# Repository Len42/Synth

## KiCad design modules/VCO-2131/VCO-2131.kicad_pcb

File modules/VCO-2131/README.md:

# Analog VCO

## 10HP Eurorack Module

### Features
- Analog VCO with sawtooth, triangle, and square/pulse outputs
- Sub-oscillator square wave output
- Pitch, modulation, PWM, and sync CV inputs
- Coarse/fine tuning knobs and +/- 2-octave switch
- Based on an [SSI2131 VCO chip](https://soundsemiconductor.com/downloads/ssi2131datasheet.pdf)
- Volt-per-octave tracking over 10 octaves
- 1V/octave input can default to the Eurorack bus CV line (jumper-selectable) - more info [here](https://lenp.net/synth/eurorack-bus-cv-gate.html)

### Notes
This module requires a 16-pin Eurorack power cable, but it does not depend on +5V power from the Eurorack system.

[Here are instructions for calibration](https://lenp.net/synth/vco-calibration.html) of the VCO for proper 1V/octave tracking.

[TODO: old link for testing](calibration.md)

PCB layouts are provided in KiCad and gerber formats.
A drilling template is provided for the front panel.

The PCBs that I used can be ordered from OSH Park. The designs are here:
- [Controls board](https://oshpark.com/shared_projects/8MjA3NoD)
- [Middle board](https://oshpark.com/shared_projects/c16FyR7y) (Note: This is an older version of the PCB. The sub-oscillator circuit does not work on this version.)
- [Back board](https://oshpark.com/shared_projects/S84ptGBY)

Please note that I am a hobbyist, not a trained electronics engineer. No guarantees!

### Software Used

[KiCad](https://www.kicad.org/) 6.0.8

<hr /><div><div style="float:left; padding-right:10px;"></div><div style="xfloat:left; padding-left:10px;"><br />© 2022 Len Popp CC BY<br />This work is licensed under a <a rel="license" href="http://creativecommons.org/licenses/by/4.0/">Creative Commons Attribution 4.0 International License</a>.</div></div>

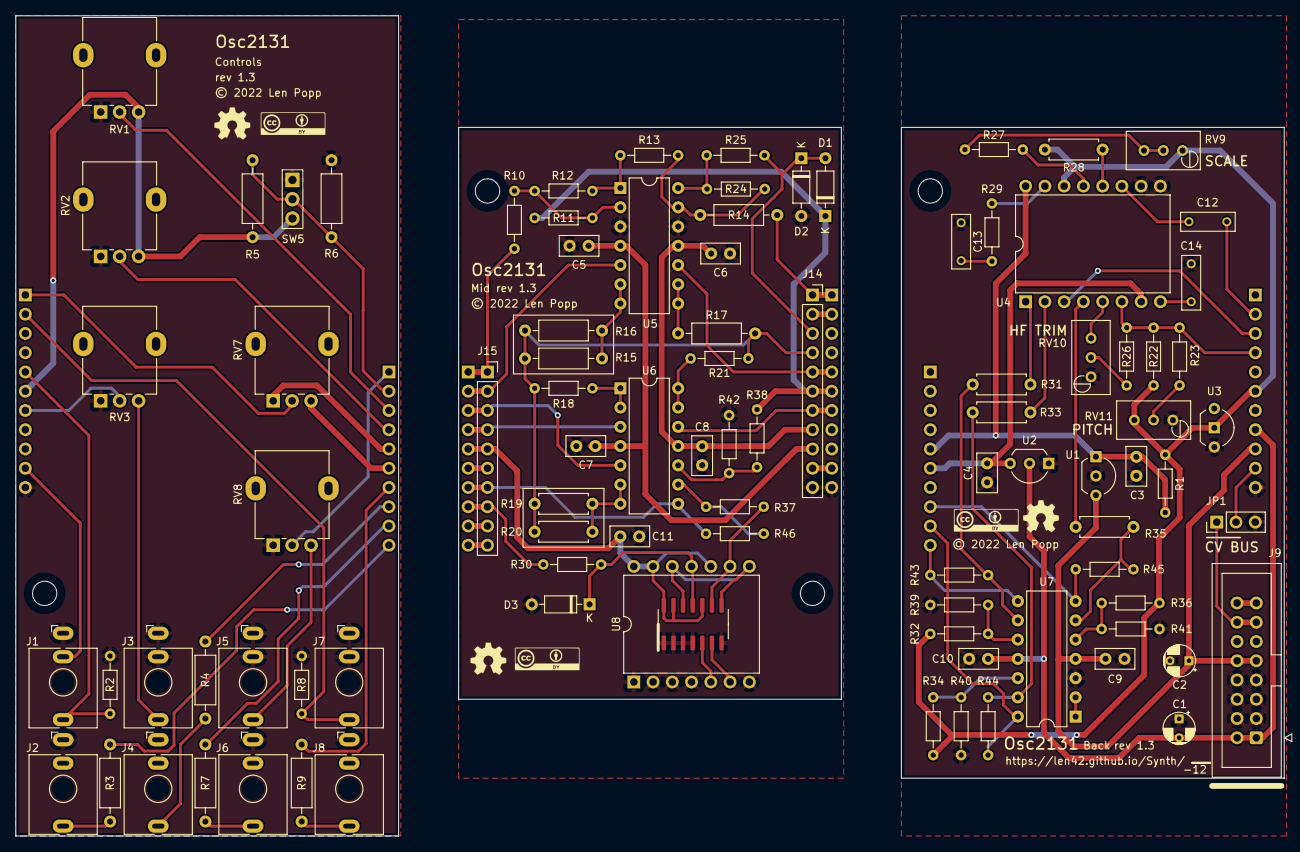
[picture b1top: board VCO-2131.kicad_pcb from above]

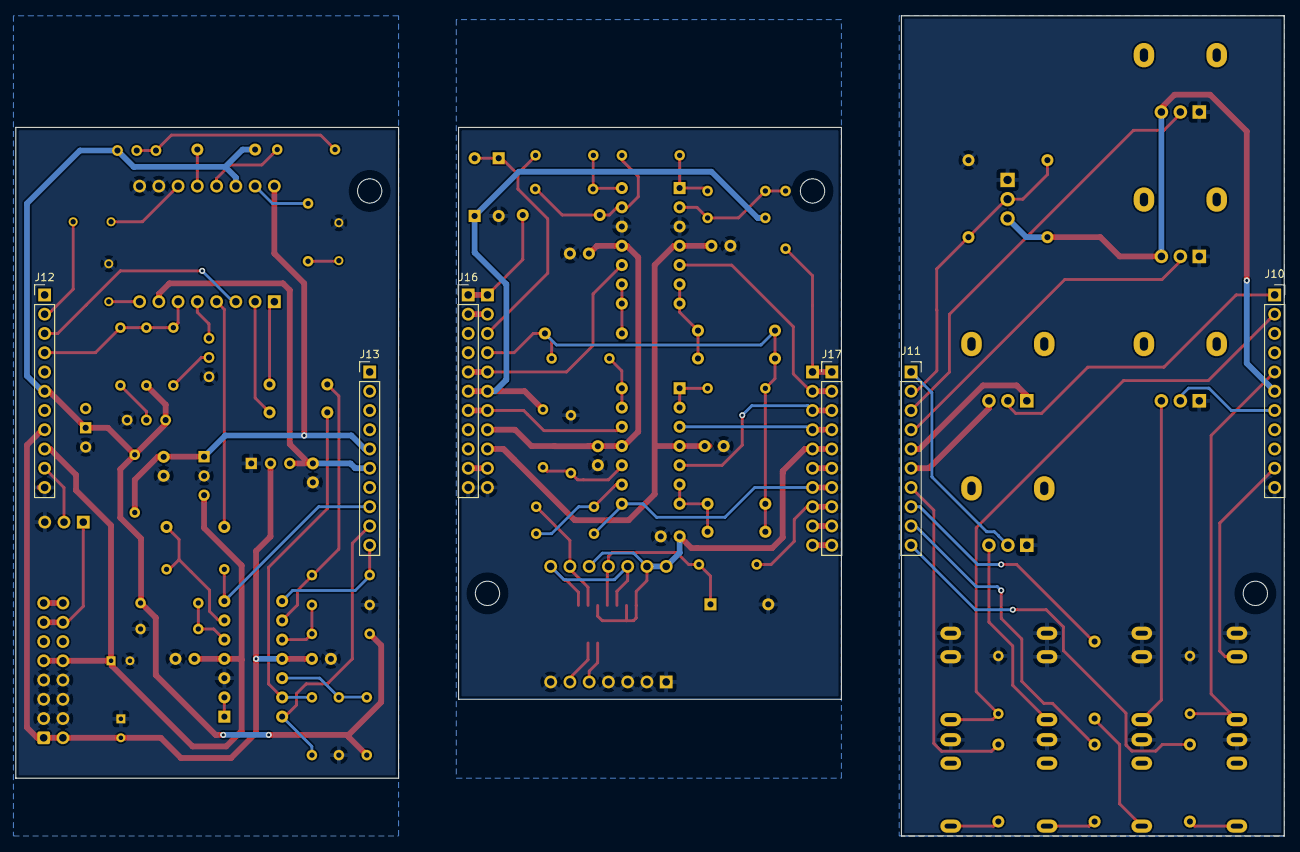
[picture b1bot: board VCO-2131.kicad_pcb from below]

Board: 2 copper layers, 167.3 x 108.2 mm, 104 parts (6 on the bottom side), 63 nets.

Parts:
C1, C2: 10U; CP_Radial_D4.0mm_P2.50mm
C3, C4, C5, C6, C7, C8, C9, C10, C11: 100N; C_Disc_D5.0mm_W2.5mm_P2.50mm
C12, C13: 10N; C_Rect_Kemet_L7.2mm_W2.5mm_P5mm
C14: 3N9; C_Rect_Kemet_L7.2mm_W2.5mm_P5mm
D1, D2, D3: 1N5711; D_DO-35_SOD27_P7.62mm_Horizontal
G1, G6: Logo_CC_BY
G2, G3, G4: Logo_OSHW
G5: Logo_CC_BY_SA; Logo_CC_BY
J1, J2, J3, J4, J5, J6, J7, J8: WQP-PJ398; Jack_3.5mm_QingPu_WQP-PJ398SM_Vertical
J9: Conn_Eurorack_16; IDC-Header-Eurorack-16-TH
J10: Conn_Front_Left; PinSocket_1x11_P2.54mm_Vertical
J11: Conn_Front_Right; PinSocket_1x10_P2.54mm_Vertical
J12: Conn_Back_Right; PinHeader_1x11_P2.54mm_Vertical
J13: Conn_Back_Left; PinHeader_1x10_P2.54mm_Vertical
J14: Conn_Passthru_Right; PinSocket_1x11_P2.54mm_Vertical
J15: Conn_Passthru_Left; PinSocket_1x10_P2.54mm_Vertical
J16: Conn_Mid_Right; PinHeader_1x11_P2.54mm_Vertical
J17: Conn_Mid_Left; PinHeader_1x10_P2.54mm_Vertical
JP1: CV-BUS; PinHeader_1x03_P2.54mm_Vertical
R1: 470R; R_Axial_DIN0204_L3.6mm_D1.6mm_P7.62mm_Horizontal
R2: 4M7; R_Axial_DIN0204_L3.6mm_D1.6mm_P7.62mm_Horizontal
R3, R4, R7, R9: 1K; R_Axial_DIN0207_L6.3mm_D2.5mm_P10.16mm_Horizontal
R5, R6, R17: 100K; R_Axial_DIN0207_L6.3mm_D2.5mm_P10.16mm_Horizontal
R8, R21, R22, R23, R25, R30: 100K; R_Axial_DIN0204_L3.6mm_D1.6mm_P7.62mm_Horizontal
R10, R13: 150K; R_Axial_DIN0204_L3.6mm_D1.6mm_P7.62mm_Horizontal
R11, R12, R24: 75K; R_Axial_DIN0204_L3.6mm_D1.6mm_P7.62mm_Horizontal
R14: 300K; R_Axial_DIN0207_L6.3mm_D2.5mm_P10.16mm_Horizontal
R15, R16: 125K; R_Axial_DIN0207_L6.3mm_D2.5mm_P10.16mm_Horizontal
R18: 62K; R_Axial_DIN0204_L3.6mm_D1.6mm_P7.62mm_Horizontal
R19, R20: 1M5; R_Axial_DIN0207_L6.3mm_D2.5mm_P7.62mm_Horizontal
R26: 270K; R_Axial_DIN0204_L3.6mm_D1.6mm_P7.62mm_Horizontal
R27: 47K; R_Axial_DIN0204_L3.6mm_D1.6mm_P7.62mm_Horizontal
R28: 499K; R_Axial_DIN0207_L6.3mm_D2.5mm_P7.62mm_Horizontal
R29: 270R; R_Axial_DIN0204_L3.6mm_D1.6mm_P7.62mm_Horizontal
R31, R33, R35: 9K; R_Axial_DIN0207_L6.3mm_D2.5mm_P7.62mm_Horizontal
R32, R34, R36, R42, R43, R44, R45, R46: 36K; R_Axial_DIN0204_L3.6mm_D1.6mm_P7.62mm_Horizontal
R37, R38: 18K; R_Axial_DIN0204_L3.6mm_D1.6mm_P7.62mm_Horizontal
R39, R40, R41: 24K; R_Axial_DIN0204_L3.6mm_D1.6mm_P7.62mm_Horizontal
RV1, RV2, RV3, RV7, RV8: 100K; Potentiometer_Alpha_RD901F-40-00D_Single_Vertical
RV9, RV10, RV11: 5K; Potentiometer_Bourns_3296W_Vertical
SW5: ON_OFF_ON; SW_SPDT_THT_2.54
U1: L78L05; TO-92_Inline_Wide
U2: L79L05; TO-92_Inline_Wide
U3: LM4040; TO-92-2_Wide
U4: SSI2131; Breakout_DIP-16_W15.24mm
U5, U6, U7: TL074; DIP-14_W7.62mm
U8: SN74HCS74; Breakout_DIP-SOIC-14_W15.24mm

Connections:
+5V: C3.1, C11.1, J11.5, J13.5, J15.5, J17.5, R1.2, RV7.1, U1.1 (VO), U4.16 (V+), U8.10 (~S), U8.13 (~R), U8.14 (VDD)
+12V: C2.1, C5.1, C7.1, C9.1, J9.9 (+12V), J9.10, J12.9, J14.9, U1.3 (VI), U5.4 (V+), U6.4 (V+), U7.4 (V+)
-5V: C4.2, J11.6, J13.6, J15.6, J17.6, RV7.3, U2.3 (VO), U4.7 (V-)
-12V: C1.2, C6.2, C8.2, C10.2, J9.1 (-12V), J9.2, J12.8, J14.8, U2.2 (VI), U5.11 (V-), U6.11 (V-), U7.11 (V-)
CV-FREQ-1VOCT: J1.T, J10.5, J14.5, J16.5, R2.1, U5.10 (+)
CV-FREQ-BUS: J1.TN, J10.10, J12.10, J14.10, J16.10, JP1.2 (C)
CV-FREQ-COARSE: J11.4, J15.4, J17.4, RV2.2, U6.3 (+)
CV-FREQ-FINE: J11.3, J15.3, J17.3, RV1.2, U6.5 (+)
CV-FREQ-MOD: J10.7, J14.7, J16.7, RV3.2, U6.12 (+)
CV-FREQ-MOD-IN: J3.T, RV3.3
CV-FREQ-OCTAVE: J11.2, J15.2, J17.2, R5.2, R6.2, SW5.2, U5.5 (+)
CV-PW-MOD: J11.1, J15.1, J17.1, R10.2, RV8.2
CV-PW-MOD-IN: J5.T, RV8.3
CV-PW-POT: J10.1, J14.1, J16.1, R14.2, RV7.2
EXPO-FREQ-2131: J12.4, J14.4, R15.1, R16.1, R17.1, R18.1, R19.1, R20.1, R21.1, R22.1, R23.1, R26.2, U4.6 (EXPO-FREQ)
GND: C1.1, C2.2, C3.2, C4.1, C5.2, C6.1, C7.2, C8.1, C9.2, C10.1, C11.2, C13.1, C14.2, D2.2 (A), D3.2 (A), J1.S, J2.S, J3.S, J3.TN, J4.S, J5.S, J5.TN, J6.S, J7.S, J7.TN, J8.S, J9.3 (GND), J9.4, J9.5 (GND), J9.6, J9.7 (GND), J9.8, J10.11, J12.11, J14.11, J16.11, JP1.3 (B), R2.2, R6.1, R8.2, R39.2, R40.2, R41.2, R42.2, RV1.1, RV2.1, RV3.1, RV8.1, RV10.1, RV11.1, SW5.1, U1.2 (GND), U2.1 (GND), U3.2 (A), U4.9 (GND), U4.10 (SYNC-H), U5.3 (+), U5.12 (+), U7.3 (+), U8.1 (~R), U8.2 (D), U8.3 (C), U8.4 (~S), U8.7 (VSS)
IN-SYNC: C12.1, J7.T, J10.2, J12.2, J14.2, J16.2, R8.1
unnamed: C12.2, U4.11 (SYNC-S)
unnamed: C13.2, R29.2
unnamed: C14.1, U4.8 (TCAP)
unnamed: J2.T, R3.2
unnamed: J4.T, R4.2
unnamed: J6.T, R7.2
unnamed: J8.T, R9.2
unnamed: J9.13 (CV), J9.14, JP1.1 (A)
unnamed: J9.15 (GATE), J9.16
unnamed: R10.1, R11.1, R12.2, U5.2 (-)
unnamed: R12.1, R13.2, U5.1
unnamed: R13.1, R14.1, R24.2, U5.13 (-)
unnamed: R15.2, R16.2, U5.6 (-), U5.7
unnamed: R17.2, U5.8, U5.9 (-)
unnamed: R18.2, U6.1, U6.2 (-)
unnamed: R19.2, R20.2, U6.6 (-), U6.7
unnamed: R21.2, U6.13 (-), U6.14
unnamed: R23.2, RV11.2
unnamed: R24.1, R25.2, U5.14
unnamed: R26.1, RV10.2
unnamed: R27.1, RV9.2, RV9.3
unnamed: R27.2, U4.13 (EXPO-SCALE)
unnamed: R28.1, U4.12 (LIN-FREQ)
unnamed: R29.1, U4.15 (BW-COMP)
unnamed: D3.1 (K), R30.2, U8.11 (C)
unnamed: R31.1, R43.2, U7.9 (-)
unnamed: R31.2, U4.1 (SAW)
unnamed: R32.1, R39.1, U7.10 (+)
unnamed: R33.1, R44.2, U7.13 (-)
unnamed: R33.2, U4.2 (PULSE)
unnamed: R34.1, R40.1, U7.12 (+)
unnamed: R35.1, R45.2, U7.6 (-)
unnamed: R35.2, U4.4 (TRI)
unnamed: R36.1, R41.1, U7.5 (+)
unnamed: R37.1, R46.2, U6.9 (-)
unnamed: R37.2, U8.9 (Q)
unnamed: R38.1, R42.1, U6.10 (+)
unnamed: RV10.3, U4.5 (HF-TRACK)
unnamed: U7.1, U7.2 (-)
unnamed: U8.8 (~Q), U8.12 (D)
OUT-PULSE: J11.9, J13.9, J15.9, J17.9, R7.1, R44.1, U7.14
OUT-SAW: J11.10, J13.10, J15.10, J17.10, R3.1, R43.1, U7.8
OUT-SUB: J11.7, J15.7, J17.7, R9.1, R46.1, U6.8
OUT-TRI: J11.8, J13.8, J15.8, J17.8, R4.1, R30.1, R45.1, U7.7
PWM-2131: D1.2 (A), D2.1 (K), J12.3, J14.3, R25.1, U4.3 (PWM)
VREF+: D1.1 (K), J10.6, J12.6, J14.6, J16.6, R1.1, R5.1, R11.2, R22.2, R28.2, R32.2, R34.2, R36.2, R38.2, RV1.3, RV2.3, RV9.1, RV11.3, SW5.3, U3.1 (K), U4.14 (VREF)

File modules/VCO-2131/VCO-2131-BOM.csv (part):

Ref,Qty,Value,Value2,Note,Description,Datasheet,Manufacturer,ManuPartNum,Distributor1,DistributorPartNum1,DistributorPartLink1,Distributor2,DistributorPartNum2,DistributorPartLink2,Distributor3,DistributorPartNum3,DistributorPartLink3
"A1","1","Cable_Eurorack_10","","Length as required","Eurorack 16-10 pin power cable","","","","Thonk","","https://www.thonk.co.uk/shop/eurorack-power-cables/","SynthCube","","https://synthcube.com/cart/eurorack-ribbon-power-cables","Modular Addict","","https://modularaddict.com/parts/eurorack-power-cables-1"
"C1 C2","2","10U","25 VDC","12 V decoupling","Capacitor - Electrolytic - 12 V decoupling","https://industrial.panasonic.com/cdbs/www-data/pdf/RDF0000/A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","Panasonic","EEA-FC1E100","Mouser","667-EEA-FC1E100","https://www.mouser.ca/ProductDetail/Panasonic/EEA-FC1E100?qs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","","","","","",""
"C3 C4 C5 C6 C7 C8 C9 C10 C11","9","100N","","IC decoupling","Capacitor - Ceramic - IC decoupling","https://product.tdk.com/system/files/dam/doc/product/capacit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","TDK","FG18X7R1H104KNT06","Mouser","810-FG18X7R1H104KNT6","https://www.mouser.ca/ProductDetail/810-FG18X7R1H104KNT6","","","","","",""
"C12 C13","2","10N","","","Capacitor - Film","https://www.mouser.ca/datasheet/2/212/1/KEM_F3101_R82-1103738.pdf","KEMET","R82EC2100SH50J","Mouser","80-R82EC2100SH50J","https://www.mouser.ca/ProductDetail/?qs=Jv4FAWB%252B0HY5NUeH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","","","","","",""
"C14","1","3N9","PPS","","Capacitor - Film","https://www.mouser.ca/datasheet/2/212/1/KEM_F3072_SMR-1103375.pdf","KEMET","SMR5392K250J01L4BULK","Mouser","80-SMR5392K250J01L4","https://www.mouser.ca/ProductDetail/KEMET/SMR5392K250J01L4BU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","","","","","",""
"D1 D2 D3","3","1N5711","","","Schottky signal diode","https://www.mouser.ca/datasheet/2/389/cd00000759-1795802.pdf","STMicroelectronics","1N5711","Mouser","511-1N5711","https://www.mouser.ca/ProductDetail/STMicroelectronics/1N571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","","","","","",""
"H1","1","Jumper_2","","","Jumper connector, 2-pin socket","https://www.mouser.ca/datasheet/2/209/KC-301174-1171759.pdf","","","Mouser","151-8013-E","https://www.mouser.ca/ProductDetail/Kobiconn/151-8013-E?qs=R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","Adafruit","3525","https://www.adafruit.com/product/3525","","",""
"H2 H4 H5 H7 H8 H9 H11 H12","8","HW_Screw_M3x0.50x6","","","Machine screw, M3x0.50x6","","","","","","","","","","","",""
"H3 H6","2","HW_Standoff_F-F_11mm_M3x0.50","","","Standoff, 11mm, female-female, M3x0.50","https://www.thonk.co.uk/wp-content/uploads/2018/05/standoff-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","Ettinger","05.03.111","Thonk","Mech_11mm_Standoff_(x10)","https://www.thonk.co.uk/shop/standoffs/","Mouser","710-970110321","https://www.mouser.ca/ProductDetail/Wurth-Elektronik/9701103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","","",""
"H10","1","HW_Front_Panel_10HP","","See drilling template","Front panel for Eurorack module, 10HP","","","","","","","","","","","",""
"J1 J2 J3 J4 J5 J6 J7 J8","8","WQP-PJ398","","","Audio Jack, 2 Poles (Mono / TS), Switched T Pole (Normalling), QingPu / Thonkiconn","http://www.qingpu-electronics.com/en/products/WQP-PJ398SM-362.html","QingPu / Thonk","PJ398SM / WQP518MA","Thonk","PJ398SM","https://www.thonk.co.uk/shop/thonkiconn/","SynthCube","WQP518MA","https://synthcube.com/cart/3-5mm-euro-jacks","Adafruit","4031","https://www.adafruit.com/product/4031"
"J9","1","Conn_Eurorack_16","","","Eurorack 16-pin board power/CV/gate bus connector","https://www.mouser.ca/datasheet/2/445/61201621621-1717735.pdf","Wurth Elektronik","61201621621","Mouser","710-61201621621","https://www.mouser.ca/ProductDetail/Wurth-Elektronik/6120162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","","","","","",""
"J10","1","Conn_Front_Left","","","Generic connector, single row, 01x11, script generated (kicad-library-utils/schlib/autogen/connector/)","","","","","","","","","","","",""
"J11","1","Conn_Front_Right","","","Generic connector, single row, 01x10, script generated (kicad-library-utils/schlib/autogen/connector/)","","","","","","","","","","","",""
"J12","1","Conn_Back_Right","","","Generic connector, single row, 01x11, script generated (kicad-library-utils/schlib/autogen/connector/)","","","","","","","","","","","",""
"J13","1","Conn_Back_Left","","","Generic connector, single row, 01x10, script generated (kicad-library-utils/schlib/autogen/connector/)","","","","","","","","","","","",""
"J14","1","Conn_Passthru_Right","","","Generic connector, single row, 01x11, script generated (kicad-library-utils/schlib/autogen/connector/)","","","","","","","","","","","",""
"J15","1","Conn_Passthru_Left","","","Generic connector, single row, 01x10, script generated (kicad-library-utils/schlib/autogen/connector/)","","","","","","","","","","","",""
"J16","1","Conn_Mid_Right","","","Generic connector, single row, 01x11, script generated (kicad-library-utils/schlib/autogen/connector/)","","","","","","","","","","","",""
"J17","1","Conn_Mid_Left","","","Generic connector, single row, 01x10, script generated (kicad-library-utils/schlib/autogen/connector/)","","","","","","","","","","","",""
"JP1","1","CV-BUS","","","Jumper pins, 3-pole, pins 1+2 closed/bridged","","","","","","","","","","","",""
"R1","1","470R","1%, 1/6 W","","Resistor","https://www.mouser.ca/datasheet/2/447/Yageo_LR_MFR_1-1714151.pdf","YAGEO","MFR-12FTF52-470R","Mouser","603-MFR-12FTF52-470R","https://www.mouser.ca/ProductDetail/YAGEO/MFR-12FTF52-470R?q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","","","","","",""
"R2","1","4M7","1%, 1/6 W","","Resistor","https://www.mouser.ca/datasheet/2/447/Yageo_LR_MFR_1-1714151.pdf","YAGEO","MFR-12FTF52-4M7","Mouser"," 603-MFR-12FTF52-4M7","https://www.mouser.ca/ProductDetail/YAGEO/MFR-12FTF52-4M7?qs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","","","","","",""
"R3 R4 R7 R9","4","1K","5%, 1/4 W","Output limiting","Resistor","https://www.mouser.ca/datasheet/2/427/ccf07-1762725.pdf","Vishay / Dale","CCF071K00JKE36","Mouser","71-CCF071K00JKE36","https://www.mouser.ca/ProductDetail/Vishay-Dale/CCF071K00JKE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","","","","","",""
"R5 R6 R17","3","100K","0.1%, 0.1 W","Input mixing","Resistor","https://www.mouser.ca/datasheet/2/427/cmfmil-1762972.pdf","Vishay / Dale","RN55C1003BRE6","Mouser","71-RN55C-B-100K/R","https://www.mouser.ca/ProductDetail/Vishay-Dale/RN55C1003BRE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","","","","","",""
"R8 R21 R22 R23 R25 R30","6","100K","1%, 1/6 W","","Resistor","https://www.mouser.ca/datasheet/2/447/Yageo_LR_MFR_1-1714151.pdf","YAGEO","MFR-12FTF52-100K","Mouser","603-MFR-12FTF52-100K","https://www.mouser.ca/ProductDetail/YAGEO/MFR-12FTF52-100K?q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","","","","","",""
"R10 R13","2","150K","1%, 1/6 W","","Resistor","https://www.mouser.ca/datasheet/2/447/Yageo_LR_MFR_1-1714151.pdf","YAGEO","MFR-12FTF52-150K","Mouser"," 603-MFR-12FTF52-150K","https://www.mouser.ca/ProductDetail/YAGEO/MFR-12FTF52-150K?q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","","","","","",""
"R11 R12 R24","3","75K","1%, 1/6 W","","Resistor","https://www.mouser.ca/datasheet/2/447/Yageo_LR_MFR_1-1714151.pdf","YAGEO","MFR-12FTF52-75K","Mouser","603-MFR-12FTF52-75K","https://www.mouser.ca/ProductDetail/YAGEO/MFR-12FTF52-75K?qs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","","","","","",""
"R14","1","300K","1%, 1/6 W","","Resistor","https://www.mouser.ca/datasheet/2/447/Yageo_LR_MFR_1-1714151.pdf","YAGEO","MFR-25FRF52-300K","Mouser","603-MFR-25FRF52-300K","https://www.mouser.ca/ProductDetail/603-MFR-25FRF52-300K","","","","","",""
"R15 R16","2","125K","0.1%, 0.1 W","Input mixing","Resistor","https://www.mouser.ca/datasheet/2/427/cmfmil-1762972.pdf","Vishay / Dale","RN55E1253BB14","Mouser","71-RN55E-B-125K","https://www.mouser.ca/ProductDetail/Vishay-Dale/RN55E1253BB1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","","","","","",""
"R18","1","62K","1%, 1/6 W","Input mixing","Resistor","https://www.mouser.ca/datasheet/2/447/Yageo_LR_MFR_1-1714151.pdf","YAGEO","MFR-12FTF52-62K","Mouser","603-MFR-12FTF52-62K","https://www.mouser.ca/ProductDetail/YAGEO/MFR-12FTF52-62K?qs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","","","","","",""
"R19 R20","2","1M5","1%, 1/6 W","","Resistor","https://www.mouser.ca/datasheet/2/447/Yageo_LR_MFR_1-1714151.pdf","YAGEO","MFR-12FTF52-1M5","Mouser","603-MFR-12FTF52-1M5","https://www.mouser.ca/ProductDetail/YAGEO/MFR-12FTF52-1M5?qs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","","","","","",""
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
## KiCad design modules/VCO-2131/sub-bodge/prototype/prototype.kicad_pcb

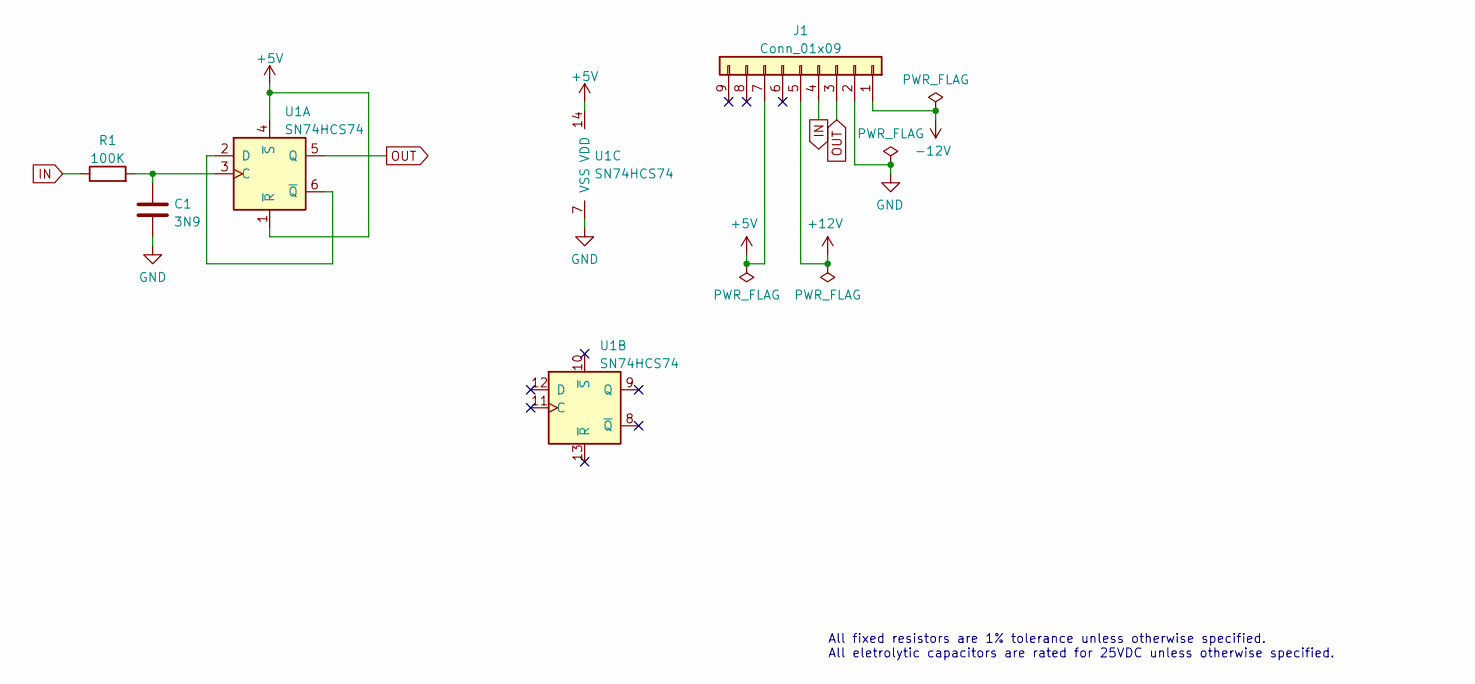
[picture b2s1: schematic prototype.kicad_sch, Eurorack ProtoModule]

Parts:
C1: 3N9; C_Rect_Kemet_L7.2mm_W2.5mm_P5mm
J1: Conn_01x09; PinHeader_1x09_P2.54mm_Vertical
R1: 100K; R_Axial_DIN0207_L6.3mm_D2.5mm_P7.62mm_Horizontal; ManufacturerPartNum MFR-12*
U1: SN74HCS74; Breakout_DIP-14_W15.24mm; ManufacturerPartNum SN74HCS74DR

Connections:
+5V: J1.7, U1.1 (~R), U1.4 (~S), U1.14 (VDD)
+12V: J1.5
-12V: J1.1
GND: C1.2, J1.2, U1.7 (VSS)
IN: J1.4, R1.1
unnamed: C1.1, R1.2, U1.3 (C)
unnamed: U1.2 (D), U1.6 (~Q)
OUT: J1.3, U1.5 (Q)

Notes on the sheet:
All fixed resistors are 1% tolerance unless otherwise specified. All eletrolytic capacitors are rated for 25VDC unless otherwise specified.

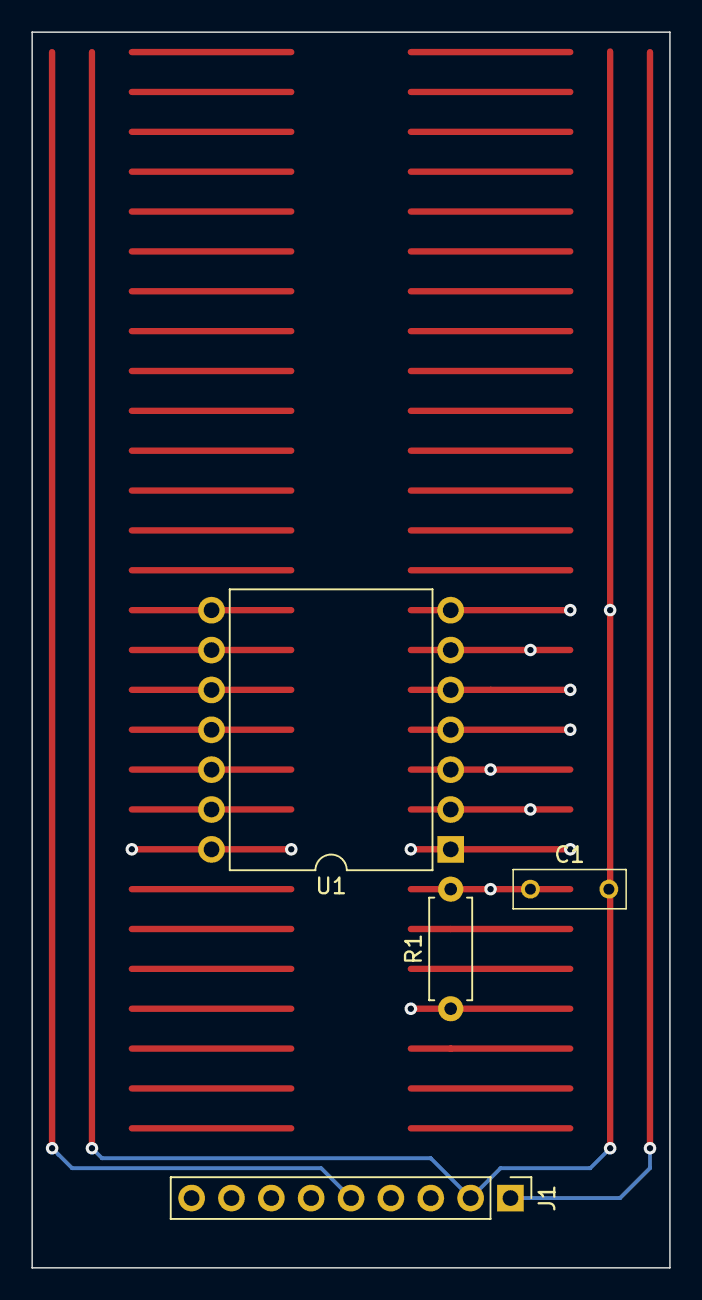
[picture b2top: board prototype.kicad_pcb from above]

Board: 6 copper layers, 40.6 x 78.7 mm, 4 parts (0 on the bottom side), 6 nets.

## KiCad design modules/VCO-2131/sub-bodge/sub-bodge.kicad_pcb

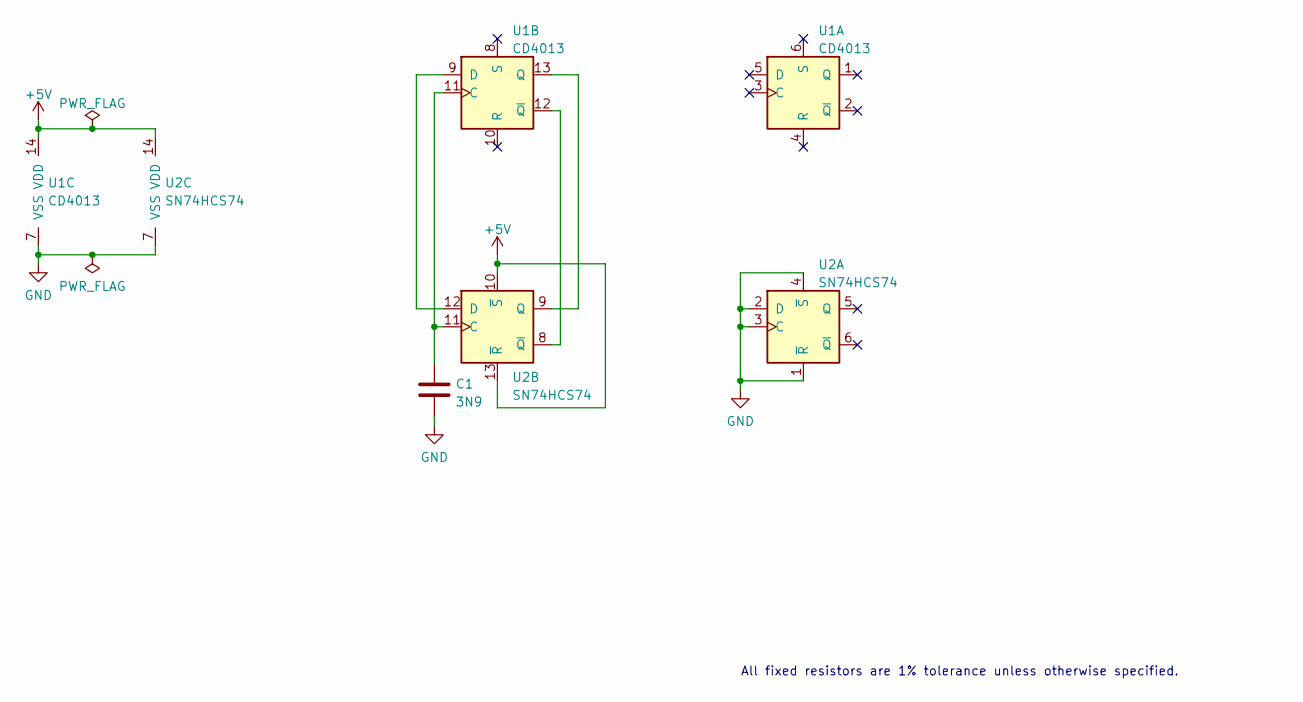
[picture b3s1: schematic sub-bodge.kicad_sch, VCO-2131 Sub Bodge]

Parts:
C1: 3N9; C_Rect_Kemet_L7.2mm_W2.5mm_P5mm
U1: CD4013; DIP-14_W7.62mm; ManufacturerPartNum CD4013BE
U2: SN74HCS74; SOIC-14_3.9x8.7mm_P1.27mm; ManufacturerPartNum SN74HCS74DR

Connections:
+5V: U1.14 (VDD), U2.10 (~S), U2.13 (~R), U2.14 (VDD)
GND: C1.2, U1.7 (VSS), U2.1 (~R), U2.2 (D), U2.3 (C), U2.4 (~S), U2.7 (VSS)
unnamed: C1.1, U1.11 (C), U2.11 (C)
unnamed: U1.9 (D), U2.12 (D)
unnamed: U1.12 (~Q), U2.8 (~Q)
unnamed: U1.13 (Q), U2.9 (Q)

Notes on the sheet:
All fixed resistors are 1% tolerance unless otherwise specified.

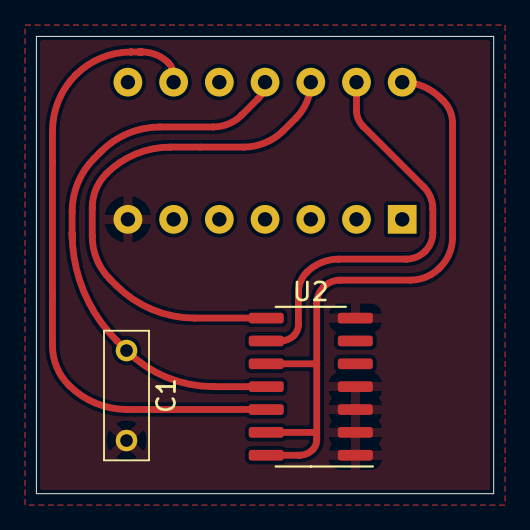
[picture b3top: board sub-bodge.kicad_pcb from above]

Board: 4 copper layers, 25.4 x 25.4 mm, 3 parts (1 on the bottom side), 6 nets.

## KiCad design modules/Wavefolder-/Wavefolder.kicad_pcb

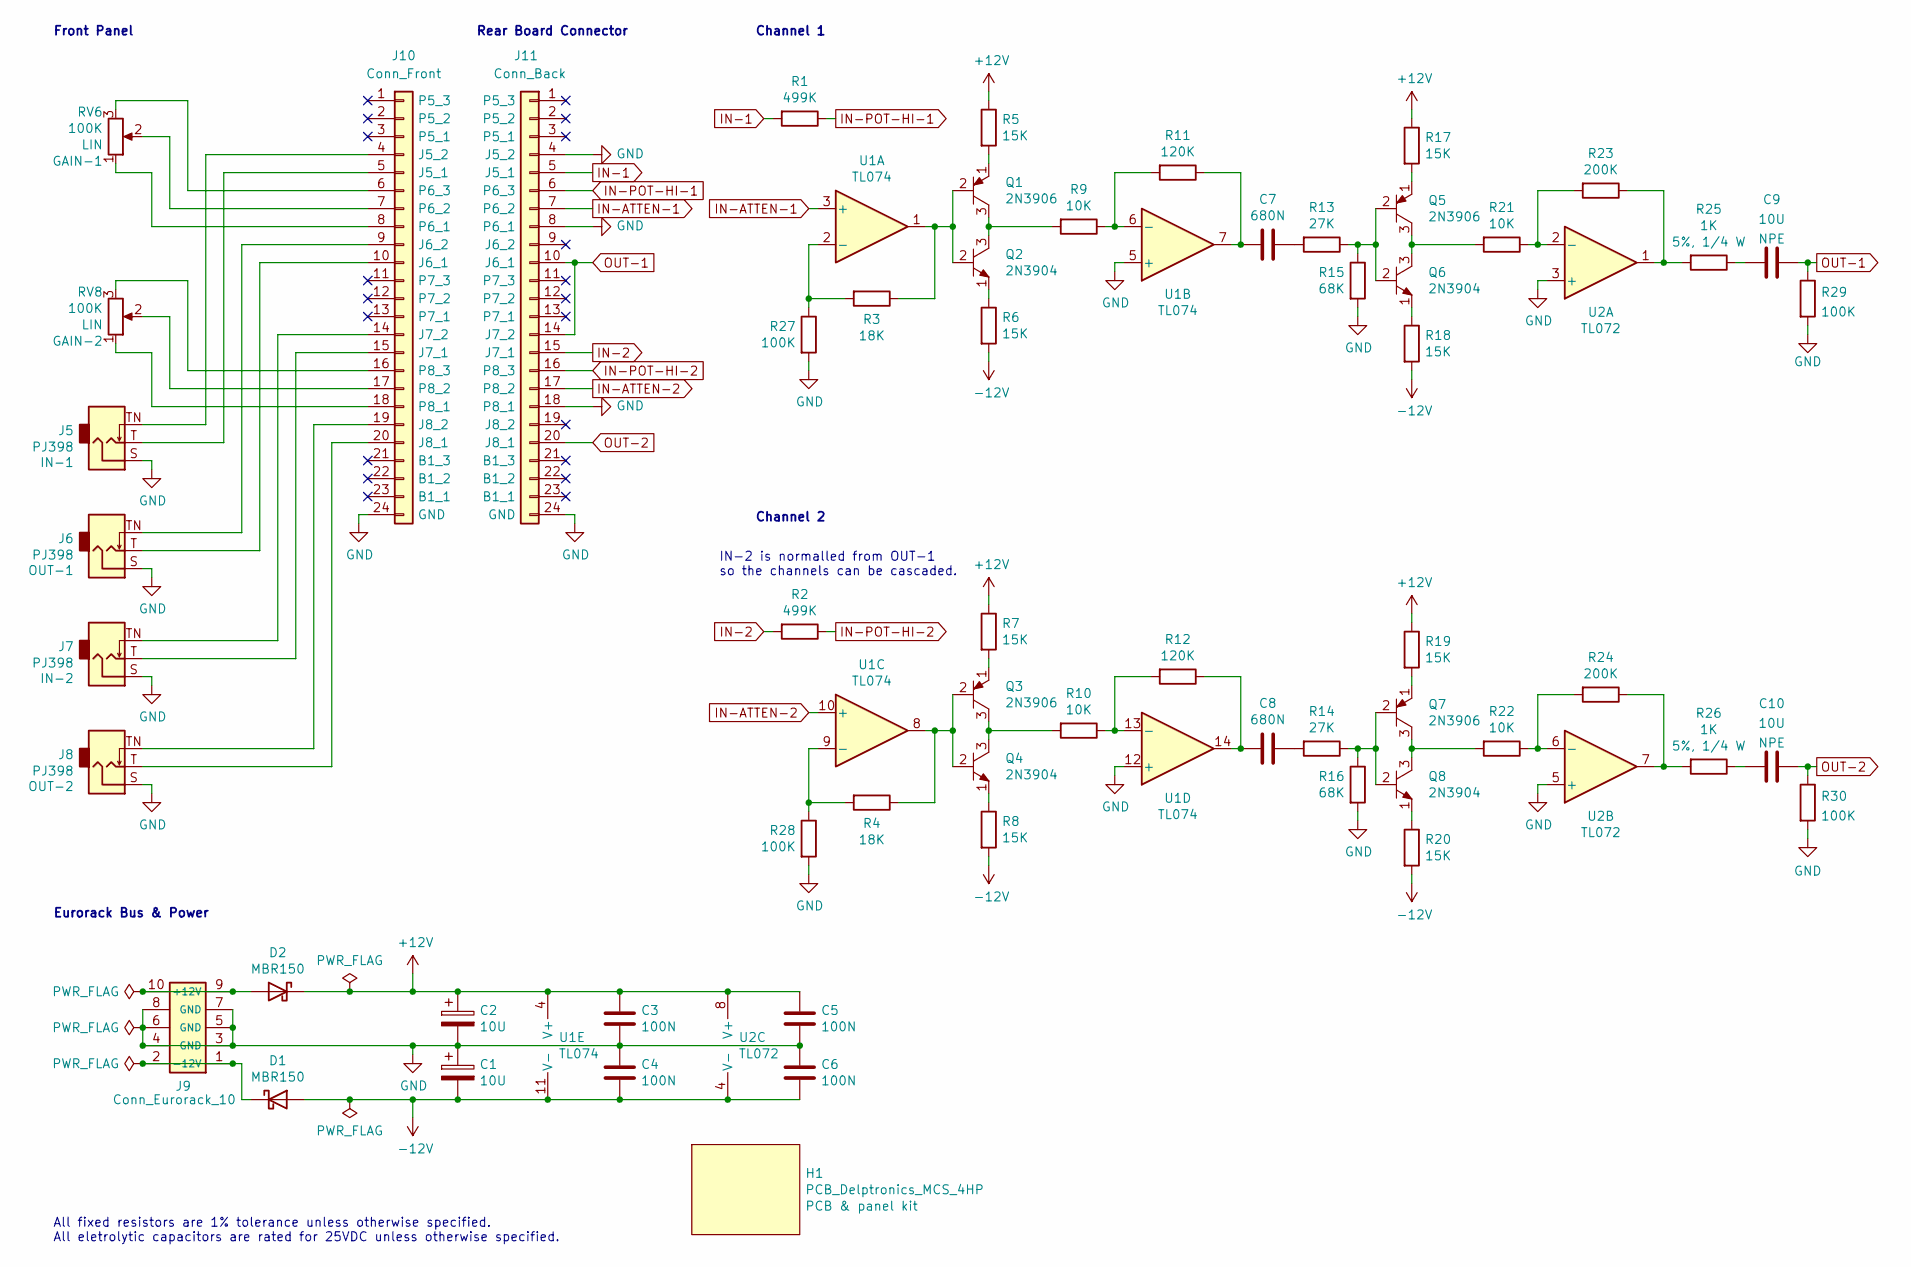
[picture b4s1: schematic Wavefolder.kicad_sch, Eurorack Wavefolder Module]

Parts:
C1, C2: 10U; CP_Radial_D5.0mm_P2.50mm; ManufacturerPartNum EEA-FC1E100
C3, C4, C5, C6: 100N; C_Disc_D5.0mm_W2.5mm_P2.50mm; ManufacturerPartNum FG18X7R1H104KNT06
C7, C8: 680N; C_Rect_L7.2mm_W4.5mm_P5.00mm; ManufacturerPartNum R82DC3680AA60K
C9, C10: 10U; C_Radial_D5.0mm_H5.0mm_P2.50mm; ManufacturerPartNum ECE-A1EN100UI
D1, D2: MBR150; D_DO-41_SOD81_P7.62mm_Horizontal; ManufacturerPartNum MBR150RLG
H1: PCB_Delptronics_MCS_4HP; NoFootprint
J5, J6, J7, J8: PJ398; Jack_3.5mm_QingPu_WQP-PJ398SM_Vertical; ManufacturerPartNum PJ398SM / WQP518MA
J9: Conn_Eurorack_10; PinHeader-Eurorack-10-TH
J10: Conn_Front; PinSocket_Delptronics_Front
J11: Conn_Back; PinHeader_Delptronics_Back_Left_4HP
Q1, Q3, Q5, Q7: 2N3906; TO-92_Inline_Wide; ManufacturerPartNum 2N3906TAR
Q2, Q4, Q6, Q8: 2N3904; TO-92_Inline_Wide; ManufacturerPartNum 2N3904 PBFREE
R1, R2: 499K; SB_Gen_1; ManufacturerPartNum MFR-25FTE52-499K
R3, R4: 18K; SB_Gen_1; ManufacturerPartNum MFR-12FTF52-18K
R5, R6, R8, R19, R20: 15K; R_Axial_DIN0207_L6.3mm_D2.5mm_P7.62mm_Horizontal; ManufacturerPartNum MFR-12FTF52-15K
R7, R17, R18: 15K; SB_Gen_2; ManufacturerPartNum MFR-12FTF52-15K
R9: 10K; SB_Gen_10; ManufacturerPartNum MFR-12FRF52-10K
R10: 10K; R_Axial_DIN0207_L6.3mm_D2.5mm_P7.62mm_Horizontal; ManufacturerPartNum MFR-12FRF52-10K
R11, R12: 120K; SB_Gen_1; ManufacturerPartNum MFR-12FTF52-120K
R13, R14: 27K; R_Axial_DIN0207_L6.3mm_D2.5mm_P7.62mm_Horizontal; ManufacturerPartNum MFR-12FTF52-27K
R15, R16: 68K; SB_Gen_1; ManufacturerPartNum MFR-12FTF52-68K
R21: 10K; SB_Gen_5; ManufacturerPartNum MFR-12FRF52-10K
R22: 10K; SB_Gen_2; ManufacturerPartNum MFR-12FRF52-10K
R23, R24: 200K; SB_Gen_1; ManufacturerPartNum MFR-12FTF52-200K
R25: 1K; R_Axial_DIN0207_L6.3mm_D2.5mm_P10.16mm_Horizontal; ManufacturerPartNum CCF071K00JKE36
R26: 1K; SB_Gen_7; ManufacturerPartNum CCF071K00JKE36
R27, R28, R29, R30: 100K; SB_Gen_1; ManufacturerPartNum MFR-12FTF52-100K
RV6, RV8: 100K; Potentiometer_Alpha_RD901F-40-00D_Single_Vertical; ManufacturerPartNum RD901F-40-15R1-B100K-00DL1
U1: TL074; DIP-14_W7.62mm_LongPads; ManufacturerPartNum TL074BCN
U2: TL072; DIP-8_W7.62mm_LongPads; ManufacturerPartNum TL072BCP

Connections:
+12V: C2.1, C3.1, C5.1, D2.1 (K), R5.1, R7.1, R17.1, R19.1, U1.4 (V+), U2.8 (V+)
-12V: C1.2, C4.2, C6.2, D1.2 (A), R6.2, R8.2, R18.2, R20.2, U1.11 (V-), U2.4 (V-)
GND: C1.1, C2.2, C3.2, C4.1, C5.2, C6.1, J5.S, J6.S, J7.S, J8.S, J9.3 (GND), J9.4, J9.5 (GND), J9.6, J9.7 (GND), J9.8, J10.24 (GND), J11.4 (J5_2), J11.8 (P6_1), J11.18 (P8_1), J11.24 (GND), R15.2, R16.2, R27.2, R28.2, R29.2, R30.2, U1.5 (+), U1.12 (+), U2.3 (+), U2.5 (+)
IN-1: J11.5 (J5_1), R1.2
IN-2: J11.15 (J7_1), R2.2
IN-ATTEN-1: J11.7 (P6_2), U1.3 (+)
IN-ATTEN-2: J11.17 (P8_2), U1.10 (+)
IN-POT-HI-1: J11.6 (P6_3), R1.1
IN-POT-HI-2: J11.16 (P8_3), R2.1
unnamed: C7.1, R13.2
unnamed: C7.2, R11.1, U1.7
unnamed: C8.1, R14.2
unnamed: C8.2, R12.1, U1.14
unnamed: C9.1, R25.1
unnamed: C10.1, R26.1
unnamed: D1.1 (K), J9.1 (-12V), J9.2
unnamed: D2.2 (A), J9.9 (+12V), J9.10
unnamed: J5.TN, J10.4 (J5_2)
unnamed: J5.T, J10.5 (J5_1)
unnamed: J10.6 (P6_3), RV6.3
unnamed: J10.7 (P6_2), RV6.2
unnamed: J10.8 (P6_1), RV6.1
unnamed: J6.TN, J10.9 (J6_2)
unnamed: J6.T, J10.10 (J6_1)
unnamed: J7.TN, J10.14 (J7_2)
unnamed: J7.T, J10.15 (J7_1)
unnamed: J10.16 (P8_3), RV8.3
unnamed: J10.17 (P8_2), RV8.2
unnamed: J10.18 (P8_1), RV8.1
unnamed: J8.TN, J10.19 (J8_2)
unnamed: J8.T, J10.20 (J8_1)
unnamed: Q1.1 (E), R5.2
unnamed: Q1.2 (B), Q2.2 (B), R3.1, U1.1
unnamed: Q1.3 (C), Q2.3 (C), R9.2
unnamed: Q2.1 (E), R6.1
unnamed: Q3.1 (E), R7.2
unnamed: Q3.2 (B), Q4.2 (B), R4.1, U1.8
unnamed: Q3.3 (C), Q4.3 (C), R10.2
unnamed: Q4.1 (E), R8.1
unnamed: Q5.1 (E), R17.2
unnamed: Q5.2 (B), Q6.2 (B), R13.1, R15.1
unnamed: Q5.3 (C), Q6.3 (C), R21.2
unnamed: Q6.1 (E), R18.1
unnamed: Q7.1 (E), R19.2
unnamed: Q7.2 (B), Q8.2 (B), R14.1, R16.1
unnamed: Q7.3 (C), Q8.3 (C), R22.2
unnamed: Q8.1 (E), R20.1
unnamed: R10.1, R12.2, U1.13 (-)
unnamed: R9.1, R11.2, U1.6 (-)
unnamed: R21.1, R23.2, U2.2 (-)
unnamed: R22.1, R24.2, U2.6 (-)
unnamed: R23.1, R25.2, U2.1
unnamed: R24.1, R26.2, U2.7
unnamed: R3.2, R27.1, U1.2 (-)
unnamed: R4.2, R28.1, U1.9 (-)
OUT-1: C9.2, J11.10 (J6_1), J11.14 (J7_2), R29.1
OUT-2: C10.2, J11.20 (J8_1), R30.1

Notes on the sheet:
Rear Board Connector
All fixed resistors are 1% tolerance unless otherwise specified. All eletrolytic capacitors are rated for 25VDC unless otherwise specified.
Channel 1
IN-2 is normalled from OUT-1 so the channels can be cascaded.
Front Panel
Channel 2
Eurorack Bus & Power

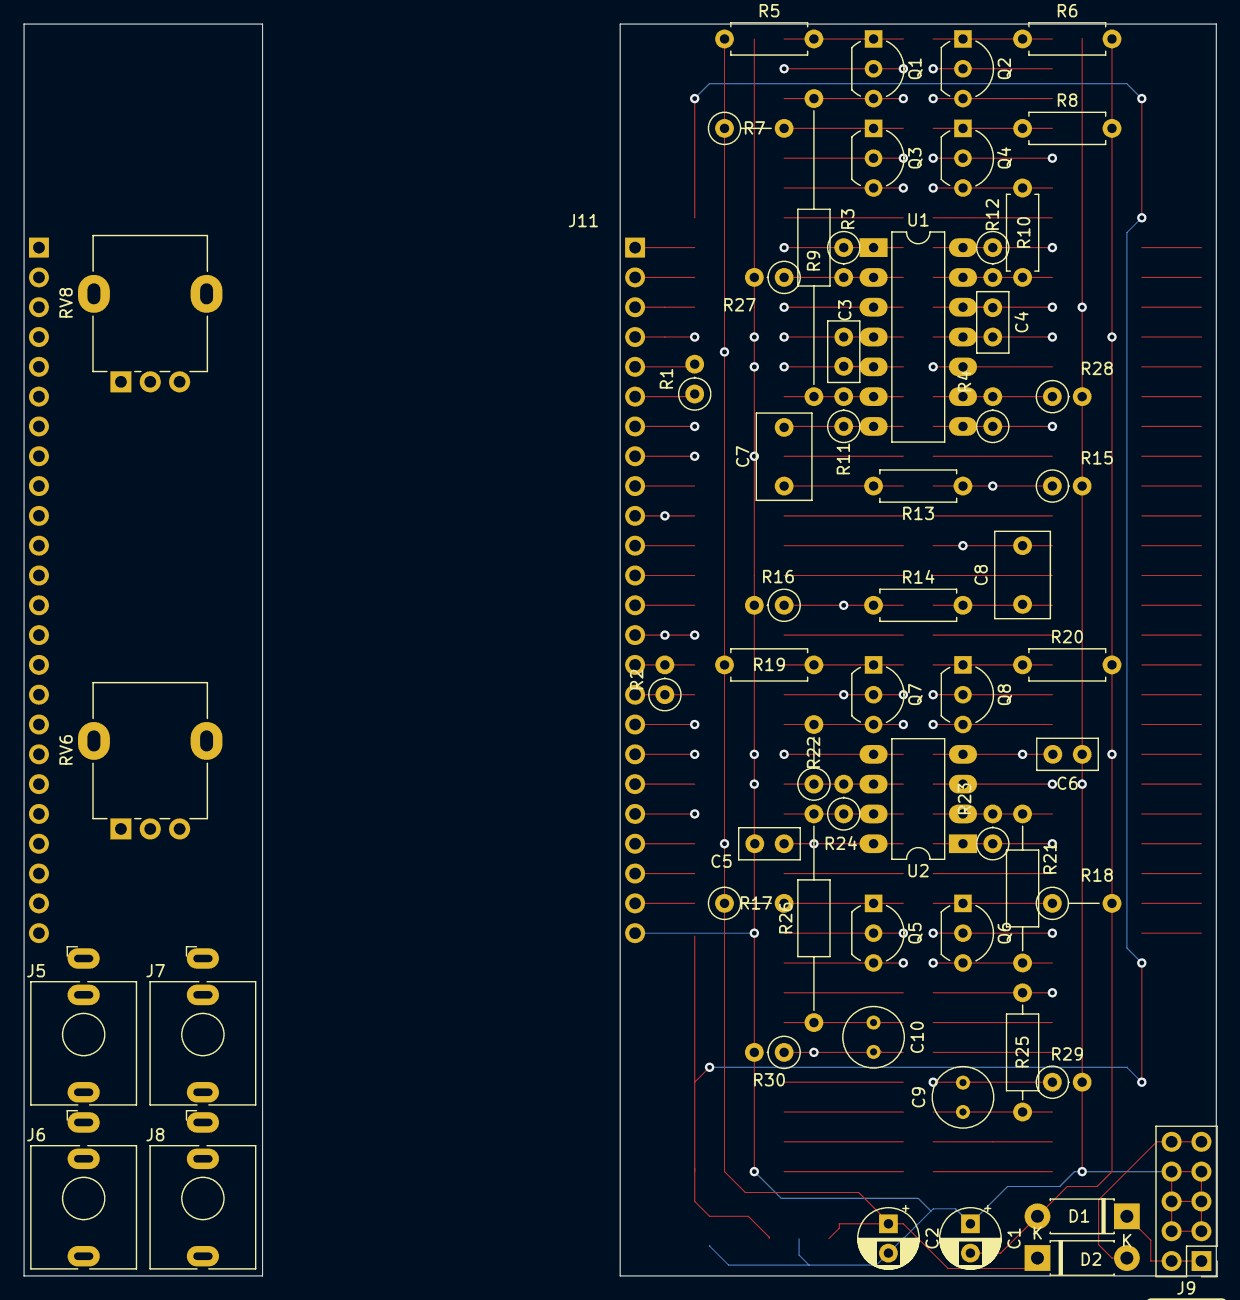
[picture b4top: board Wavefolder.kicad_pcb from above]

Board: 6 copper layers, 50.8 x 106.7 mm, 61 parts (1 on the bottom side), 57 nets.

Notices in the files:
modules/VCO-2131/VCO-2131.kicad_pcb:
Copyright © 2022 Len Popp CC BY
modules/Wavefolder-/Wavefolder.kicad_pcb:
Copyright © 2021 Len Popp CC BY
